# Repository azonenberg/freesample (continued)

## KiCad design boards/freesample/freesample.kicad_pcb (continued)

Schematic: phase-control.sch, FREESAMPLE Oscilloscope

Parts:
C163, C164, C175: 4.7 uF; EIA_0603_CAP_NOSILK
C165, C168, C173, C174: 100 pF; EIA_0201_CAP_NOSILK
C166, C167, C169, C170, C171, C172: 0.47 uF; EIA_0402_CAP_NOSILK
C263, C264, C265, C266, C267, C268, C269, C270, C271, C272, C273, C274, C291, C292: 530Z104KT10T; EIA_0201_CAP_NOSILK
R19: 165K; EIA_0402_RES_NOSILK
R20: 100K; EIA_0402_RES_NOSILK
R21: 10; EIA_0402_RES_NOSILK
R76, R77, R78, R79, R80, R81, R82, R104, R105: 10K; EIA_0402_RES_NOSILK
R83, R95: 127; EIA_0402_RES_NOSILK
R84, R96: 82; EIA_0402_RES_NOSILK
U16: HMC856; QFN_32_0.5MM_5x5MM
U17: NB6L295; QFN_24_0.5MM_4x4MM

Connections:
/3V3: C163.1, C166.1, C167.1, C169.1, C170.1, C171.1, C172.1, R19.2, R81.2, R83.2, R95.2, U17.1 (VCC), U17.6 (VCC), U17.8 (IN1_P), U17.12 (VCC1), U17.15 (VCC1), U17.16 (VCC0), U17.19 (VCC0); also elsewhere on the board
/3V3_N: C164.1, C165.1, C168.1, R20.1, R76.1, R77.1, R78.1, R79.1, R80.1, U16.27 (VEE), U16.30 (VEE), U16.PAD (VEE); also elsewhere on the board
/COARSE_EN: R104.1, U17.2 (~EN); also elsewhere on the board
/COARSE_SCLK: U17.5 (SCLK); also elsewhere on the board
/COARSE_SDIN: U17.4 (SDIN); also elsewhere on the board
/COARSE_SLOAD: R105.1, U17.3 (SLOAD); also elsewhere on the board
/FINE_SEL0_N: C264.2; also elsewhere on the board
/FINE_SEL0_P: C263.2; also elsewhere on the board
/FINE_SEL1_N: C272.2; also elsewhere on the board
/FINE_SEL1_P: C271.2; also elsewhere on the board
/FINE_SEL2_N: C266.2; also elsewhere on the board
/FINE_SEL2_P: C265.2; also elsewhere on the board
/FINE_SEL3_N: C274.2; also elsewhere on the board
/FINE_SEL3_P: C273.2; also elsewhere on the board
/FINE_SEL4_N: C268.2; also elsewhere on the board
/FINE_SEL4_P: C267.2; also elsewhere on the board
/GND: C163.2, C164.2, C165.2, C166.2, C167.2, C168.2, C169.2, C170.2, C171.2, C172.2, C173.1, C174.1, C175.1, R21.1, R82.2, R84.2, R96.2, R104.2, R105.2, U16.1 (GND), U16.4 (GND), U16.5 (GND), U16.11 (GND), U16.14 (GND), U16.20 (GND), U16.21 (GND), U16.24 (GND), U16.26 (GND), U16.31 (GND), U17.11 (GND), U17.20 (GND), U17.21 (VT0), U17.24 (VT0), U17.PAD (GND); also elsewhere on the board
/Phase control/CLKIN0_AC_N: C270.1, U16.3 (IN_N)
/Phase control/CLKIN0_AC_P: C269.1, U16.2 (IN_P)
/Phase control/CLKIN0_N: C270.2; also elsewhere on the board
/Phase control/CLKIN0_P: C269.2; also elsewhere on the board
/Phase control/CLKIN1_AC_N: C292.1, U17.23 (IN0_P)
/Phase control/CLKIN1_AC_P: C291.1, U17.22 (IN0_N)
/Phase control/CLKIN1_N: C292.2; also elsewhere on the board
/Phase control/CLKIN1_P: C291.2; also elsewhere on the board
/Phase control/COARSEPHASE_N: R95.1, R96.1, U17.18 (Q0_P); also elsewhere on the board
/Phase control/COARSEPHASE_P: R83.1, R84.1, U17.17 (Q0_N); also elsewhere on the board
/Phase control/DELAY_VR: C173.2, C174.2, C175.2, R19.1, R20.2, U16.28 (VR)
/Phase control/FINEPHASE_N: U16.22 (OUT_N); also elsewhere on the board
/Phase control/FINEPHASE_P: U16.23 (OUT_P); also elsewhere on the board
/Phase control/FS0_AC_N: C264.1, R76.2, U16.7 (B0_N)
/Phase control/FS0_AC_P: C263.1, U16.6 (B0_P)
/Phase control/FS1_AC_N: C272.1, R77.2, U16.10 (B1_N)
/Phase control/FS1_AC_P: C271.1, U16.9 (B1_P)
/Phase control/FS2_AC_N: C266.1, R78.2, U16.13 (B2_N)
/Phase control/FS2_AC_P: C265.1, U16.12 (B2_P)
/Phase control/FS3_AC_N: C274.1, R79.2, U16.16 (B3_N)
/Phase control/FS3_AC_P: C273.1, U16.15 (B3_P)
/Phase control/FS4_AC_N: C268.1, R80.2, U16.18 (B4_N)
/Phase control/FS4_AC_P: C267.1, U16.19 (B4_P)
unnamed: R21.2, U16.29 (VB_GND)
unnamed: R81.1, R82.1, U17.9 (IN1_N)

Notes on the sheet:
-1200 to +400 mV -> 500 to 1350 mV p-p
-800 mV gives 700 mV p-p output
Need nonzero differential on IN1 per datasheet footnote 1 on page 3. IN1_N must be 1050 to 3150 mV so we can't just ground it.
Fine delay line for PLL/CDR mode (1 Tsps max when combined w/ LMK04806)
Coarse delay line for non-repetitive triggers (90 GSa/s max)
NOTE: FINE_SEL inputs are AC coupled despite being slow. This effectively makes them dynamic logic. To prevent invalid states from appearing on on the input buffers, the FPGA must periodically invert the delay value and return to the desired value, during the dead time in between acquisitions. Calc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
We want FS* to default to 5'b11111 at power up. Terminator is 600R to ground on both sides. P side is left floating so terminator pulls it high. 10K gives us -186 mV at the N side.
LVPECL Thevenin load resistors
P/N swap input and output for routability

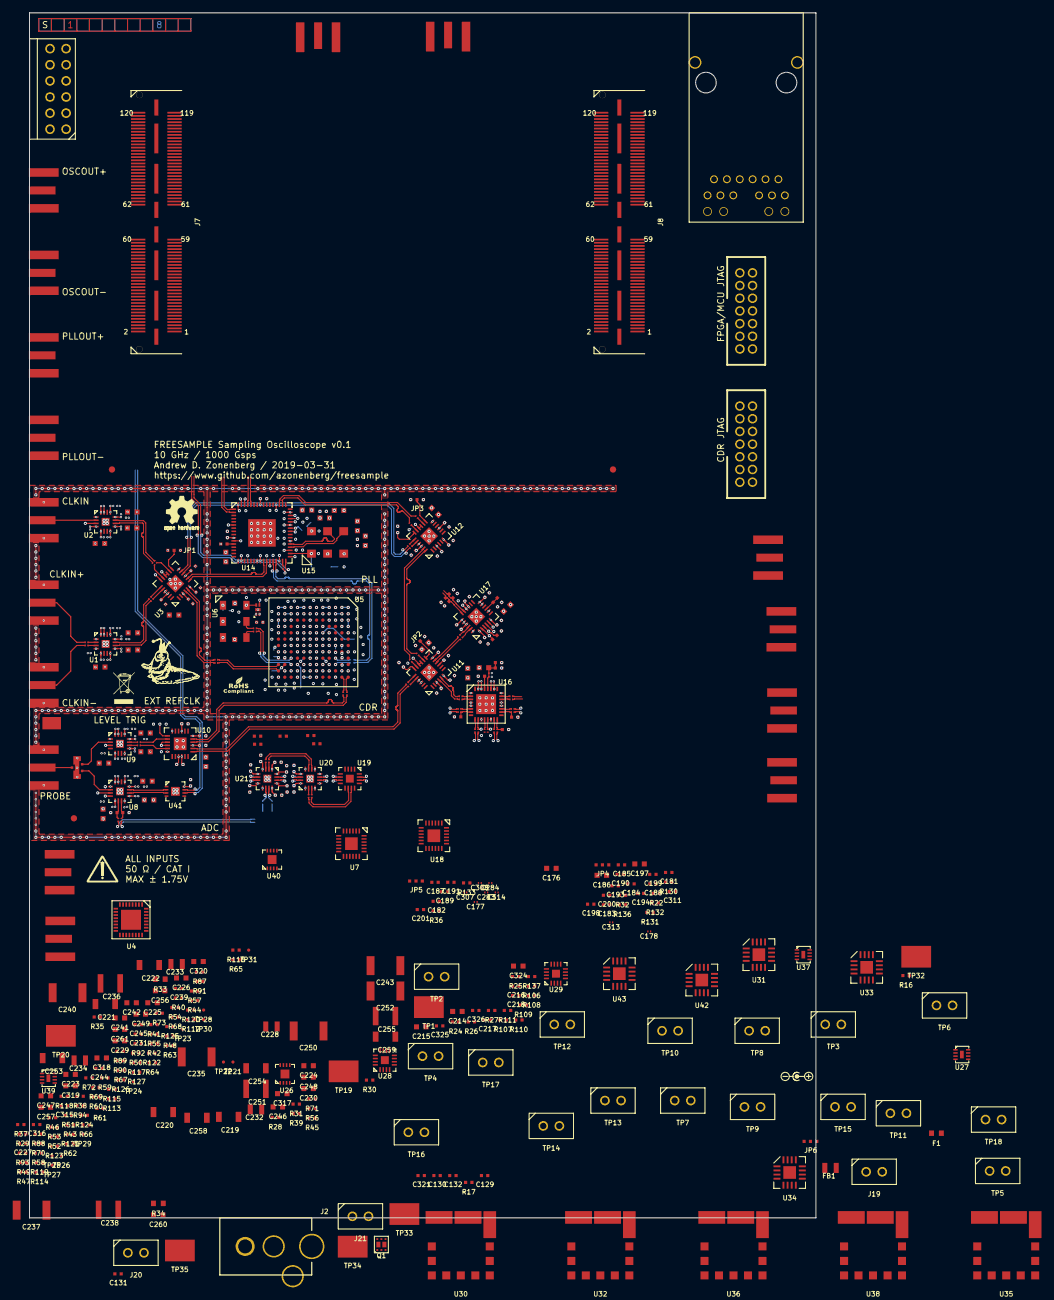
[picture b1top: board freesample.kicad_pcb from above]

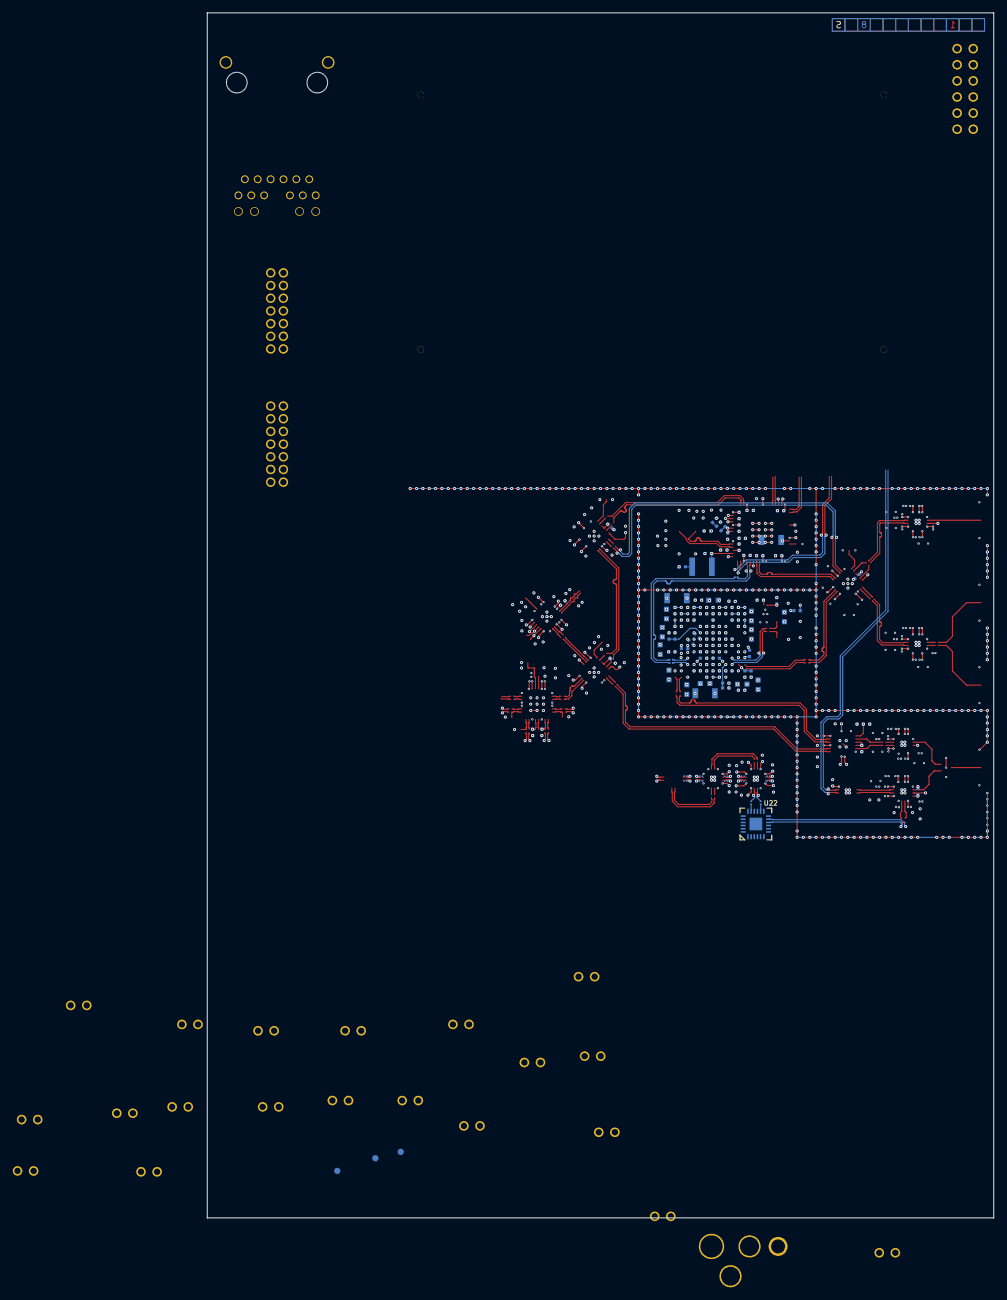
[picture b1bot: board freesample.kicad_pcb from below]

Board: 8 copper layers, 124.0 x 190.0 mm, 577 parts (109 on the bottom side), 389 nets.

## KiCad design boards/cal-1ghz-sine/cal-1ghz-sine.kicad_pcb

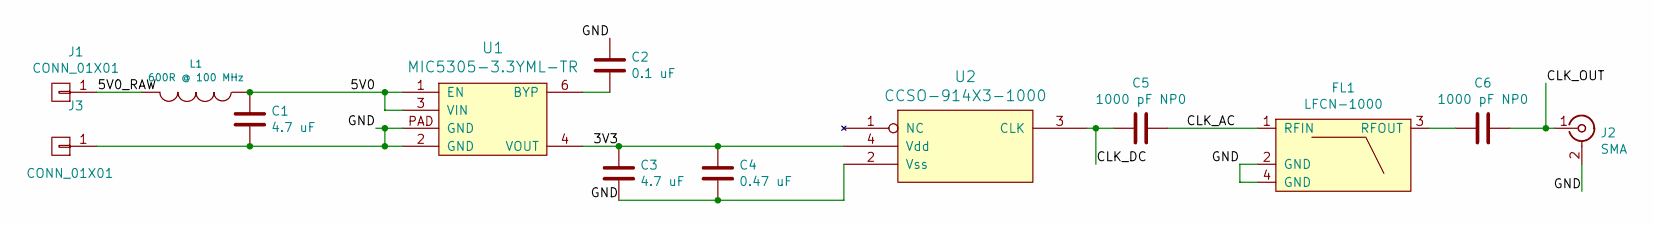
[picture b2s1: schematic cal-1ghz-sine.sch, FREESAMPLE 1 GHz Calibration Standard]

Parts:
C1, C3: 4.7 uF; EIA_0603_CAP_NOSILK
C2: 0.1 uF; EIA_0402_CAP_NOSILK
C4: 0.47 uF; EIA_0402_CAP_NOSILK
C5, C6: 1000 pF NP0; EIA_0402_CAP_NOSILK
FL1: LFCN-1000; FILTER_MINICIRCUITS_LFCN
J1, J3: CONN_01X01; TESTPOINT_SMT_KEYSTONE_5016
J2: SMA; CONN_SMA_EDGE_SAMTEC_SMA_J_P_H_ST_EM1
L1: 600R @ 100 MHz; EIA_0402_CAP_NOSILK
U1: MIC5305-3.3YML-TR; DFN_6_0.65MM_2x2MM
U2: CCSO-914X3-1000; OSC_CRYSTEK_CCSO-914X3

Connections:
/3V3: C3.1, C4.1, U1.4 (VOUT), U2.4 (Vdd)
/5V0: C1.1, L1.1, U1.1 (EN), U1.3 (VIN)
/5V0_RAW: J1.1, L1.2
/CLK_AC: C5.1, FL1.1 (RFIN)
/CLK_DC: C5.2, U2.3 (CLK)
/CLK_OUT: C6.1, J2.1 (In)
/GND: C1.2, C2.1, C3.2, C4.2, FL1.2 (GND), FL1.4 (GND), J2.2 (Ext), J3.1, U1.2 (GND), U1.PAD (GND), U2.2 (Vss)
unnamed: C2.2, U1.6 (BYP)
unnamed: C6.2, FL1.3 (RFOUT)

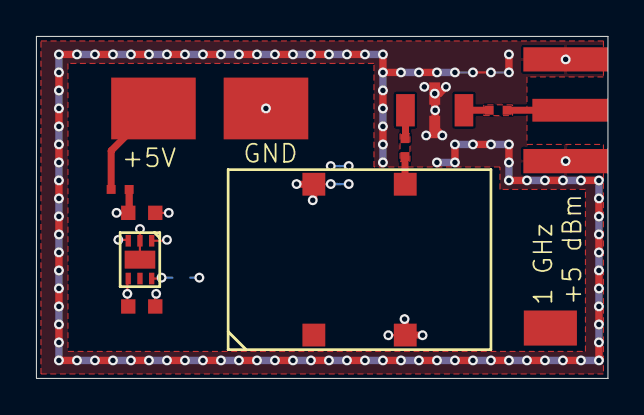
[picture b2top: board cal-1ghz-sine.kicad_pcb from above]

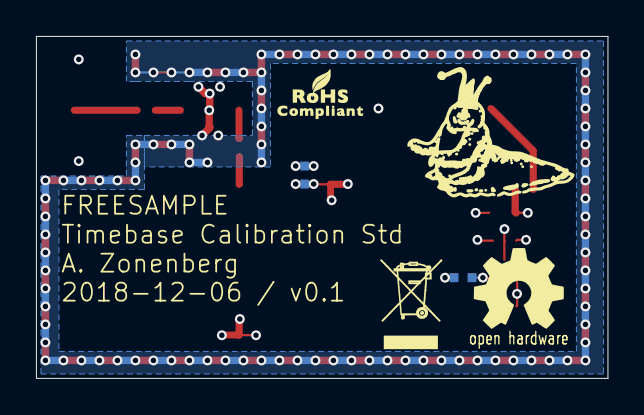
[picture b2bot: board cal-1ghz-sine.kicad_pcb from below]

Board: 4 copper layers, 31.8 x 19.0 mm, 13 parts (2 on the bottom side), 9 nets.

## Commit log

2018-11-16 Initial implementation of simulator
2018-11-16 Updated simulator
2018-12-05 Initial microstrip layout for cal board
2018-12-07 Finished initial version of cal-1ghz-sine board. Sending to fab.
2018-12-16 Updated ignore properties
2018-12-16 Initial version of main FREESAMPLE board schematic
2018-12-17 Continued initial schematic capture
2018-12-23 Continued initial schematic entry
2019-02-18 Continued work on schematic capture
2019-02-24 Continued work on FREESAMPLE schematic including PSU.
2019-02-24 Lots more work on PSU and sch readability improvements
2019-02-27 Continued work on PSU design
2019-02-27 Hooked up new power rails
2019-03-01 Continued PSU design
2019-03-11 Continued schematic capture work. Hooked up most SoM connectors.
2019-03-11 Lots of ERC fixes, added CML-to-LVDS buffers for FPGA input signals
2019-03-12 Finished PSU schematic. Ready for design review!
2019-03-14 Specified part number for AC coupling caps
2019-03-14 Began design review. Added review status checklist with current progress. Added some test points, plus an attenuator on the DAC output to prevent bad firmware from damaging the comparators
2019-03-15 Updated schematic to KiCAD 5.1 release
2019-03-15 Initial fab notes
2019-03-15 Updated fab notes with stackup info
2019-03-15 Removed internal notes that aren't needed anymore
2019-03-15 Added more onfo about impedances to fab notes
2019-03-15 Updated stackup for core-out construction
2019-03-15 Updated with Saturn calculations for new stackup
2019-03-15 Removed "recalculate these" note
2019-03-16 Added more test points. Started picking packages for passives. Continued schematic review.
2019-03-16 Continued schematic review
2019-03-16 Continued assigning footprints
2019-03-16 Continued selecting component footprints and working on schematic review
2019-03-17 Continued schematic review. Added more decoupling to DAC
2019-03-17 Continued design review. Added test points on all power rails.
2019-03-17 Continued schematic review. Significantly simplified one-shot to reduce jitter, board area, and power consumption
2019-03-17 Continued design review. Changed termination on DFFs to 1V8. Added some pull resistors to keep DFFs in reset during boot.
2019-03-17 Continued work on schematic review. Added some more pull resistors.
2019-03-17 Finished schematic review. Added a bunch more test points. Need to make a few footprints then ready for layout!
2019-03-17 Added fiducials
2019-03-19 Initial layout of external refclks block
2019-03-19 Began layout on clock recovery block
2019-03-21 Finished initial layout of CDR subsystem
2019-03-21 Moved CDR block down so it's closer to the level trigger
2019-03-21 Swapped clock inputs to TLK10232 to reduce via count. Began PLL layout.
2019-03-21 Finished initial PLL layout
2019-03-21 Tweaks to PLL and CDR layout, swapped a few signals around. Began work on level trigger and ADC layout.
2019-03-21 Continued layout on level trigger subsystem
2019-03-23 Finished initial layout of level trigger and ADC subsystems
2019-03-24 Continued layout on clock muxing
2019-03-25 Initial layout of coarse delay line
2019-03-25 Rearranged a bunch of pending stuff in preparation for further layout. Moved SMAs to approximate final locations
2019-03-28 Finished initial layout of delay lines
2019-04-01 Initial layout work on one-shot. Nowhere near done.
